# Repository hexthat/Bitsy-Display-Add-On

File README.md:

# Bitsy-Display-Add-On
OLED display for Adafruit's [ItsyBitsy](https://www.adafruit.com/?q=itsybitsy&sort=BestMatch)

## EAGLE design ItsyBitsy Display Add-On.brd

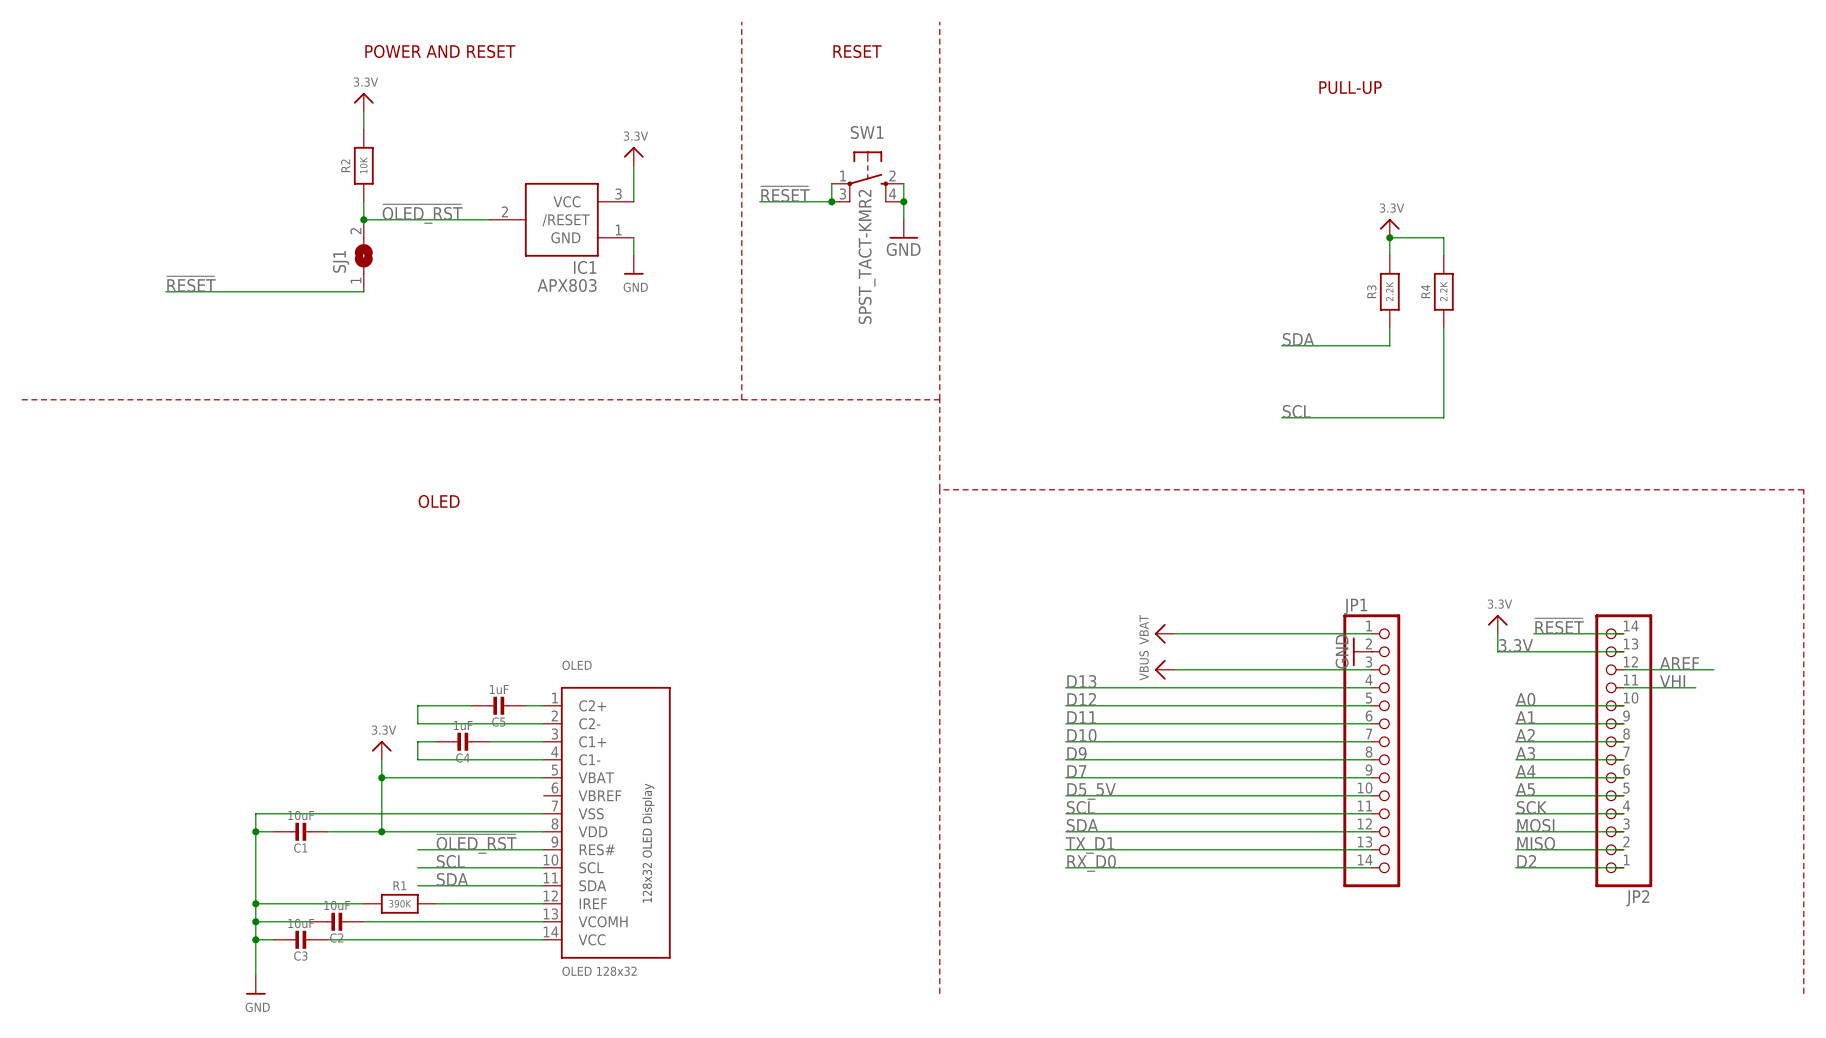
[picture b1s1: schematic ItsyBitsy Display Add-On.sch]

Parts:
C1, C2, C3: 10uF; 0805-NO
C4, C5: 1uF; 0805-NO
IC1: APX803; SOT23
JP1, JP2: HEADER-1X14; 1X14_ROUND70
OLED: OLED 128x32; UG-2832HSWEG02_WRAPUNDER
R1: 390K; 0805-NO
R2: 10K; _0805MP
R3, R4: 2.2K; 0805-NO
SJ1: SOLDERJUMPER; SOLDERJUMPER_ARROW_NOPASTE
SW1: SPST_TACT-KMR2; KMR2

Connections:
3.3V: C1.2, IC1.3 (VCC), JP2.13, OLED.5 (VBAT), OLED.8 (VDD), R2.2, R3.2, R4.2
!OLED_RST: IC1.2 (/RESET), OLED.9 (RES#), R2.1, SJ1.2
!RESET: JP2.14, SJ1.1, SW1.1, SW1.3 (P1)
A0: JP2.10
A1: JP2.9
A2: JP2.8
A3: JP2.7
A4: JP2.6
A5: JP2.5
AREF: JP2.12
C1N: C4.1, OLED.4 (C1-)
C1P: C4.2, OLED.3 (C1+)
C2N: C5.1, OLED.2 (C2-)
C2P: C5.2, OLED.1 (C2+)
D2: JP2.1
D5_5V: JP1.10
D7: JP1.9
D9: JP1.8
D10: JP1.7
D11: JP1.6
D12: JP1.5
D13: JP1.4
GND: C1.1, C2.1, C3.1, IC1.1 (GND), JP1.2, OLED.7 (VSS), R1.1, SW1.2 (S), SW1.4 (S1)
IREF: OLED.12 (IREF), R1.2
MISO: JP2.2
MOSI: JP2.3
RX_D0: JP1.14
SCK: JP2.4
SCL: JP1.11, OLED.10 (SCL), R4.1
SDA: JP1.12, OLED.11 (SDA), R3.1
TX_D1: JP1.13
VBAT: JP1.1
VBREF: OLED.6 (VBREF)
VBUS: JP1.3
VCC: C3.2, OLED.14 (VCC)
VCOMH: C2.2, OLED.13 (VCOMH)
VHI: JP2.11

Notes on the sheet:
POWER AND RESET
RESET
PULL-UP
OLED

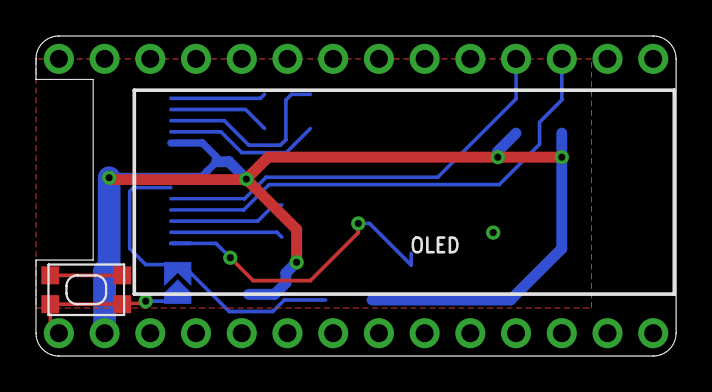
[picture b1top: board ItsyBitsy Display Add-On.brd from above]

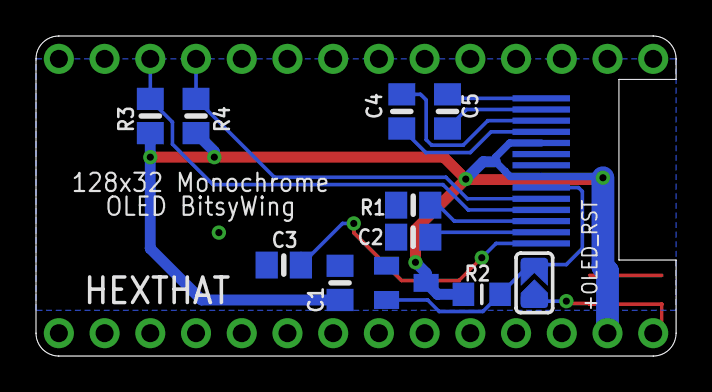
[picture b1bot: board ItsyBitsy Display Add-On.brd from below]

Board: 2 copper layers, 35.6 x 17.8 mm, 15 parts (11 on the bottom side), 13 nets.

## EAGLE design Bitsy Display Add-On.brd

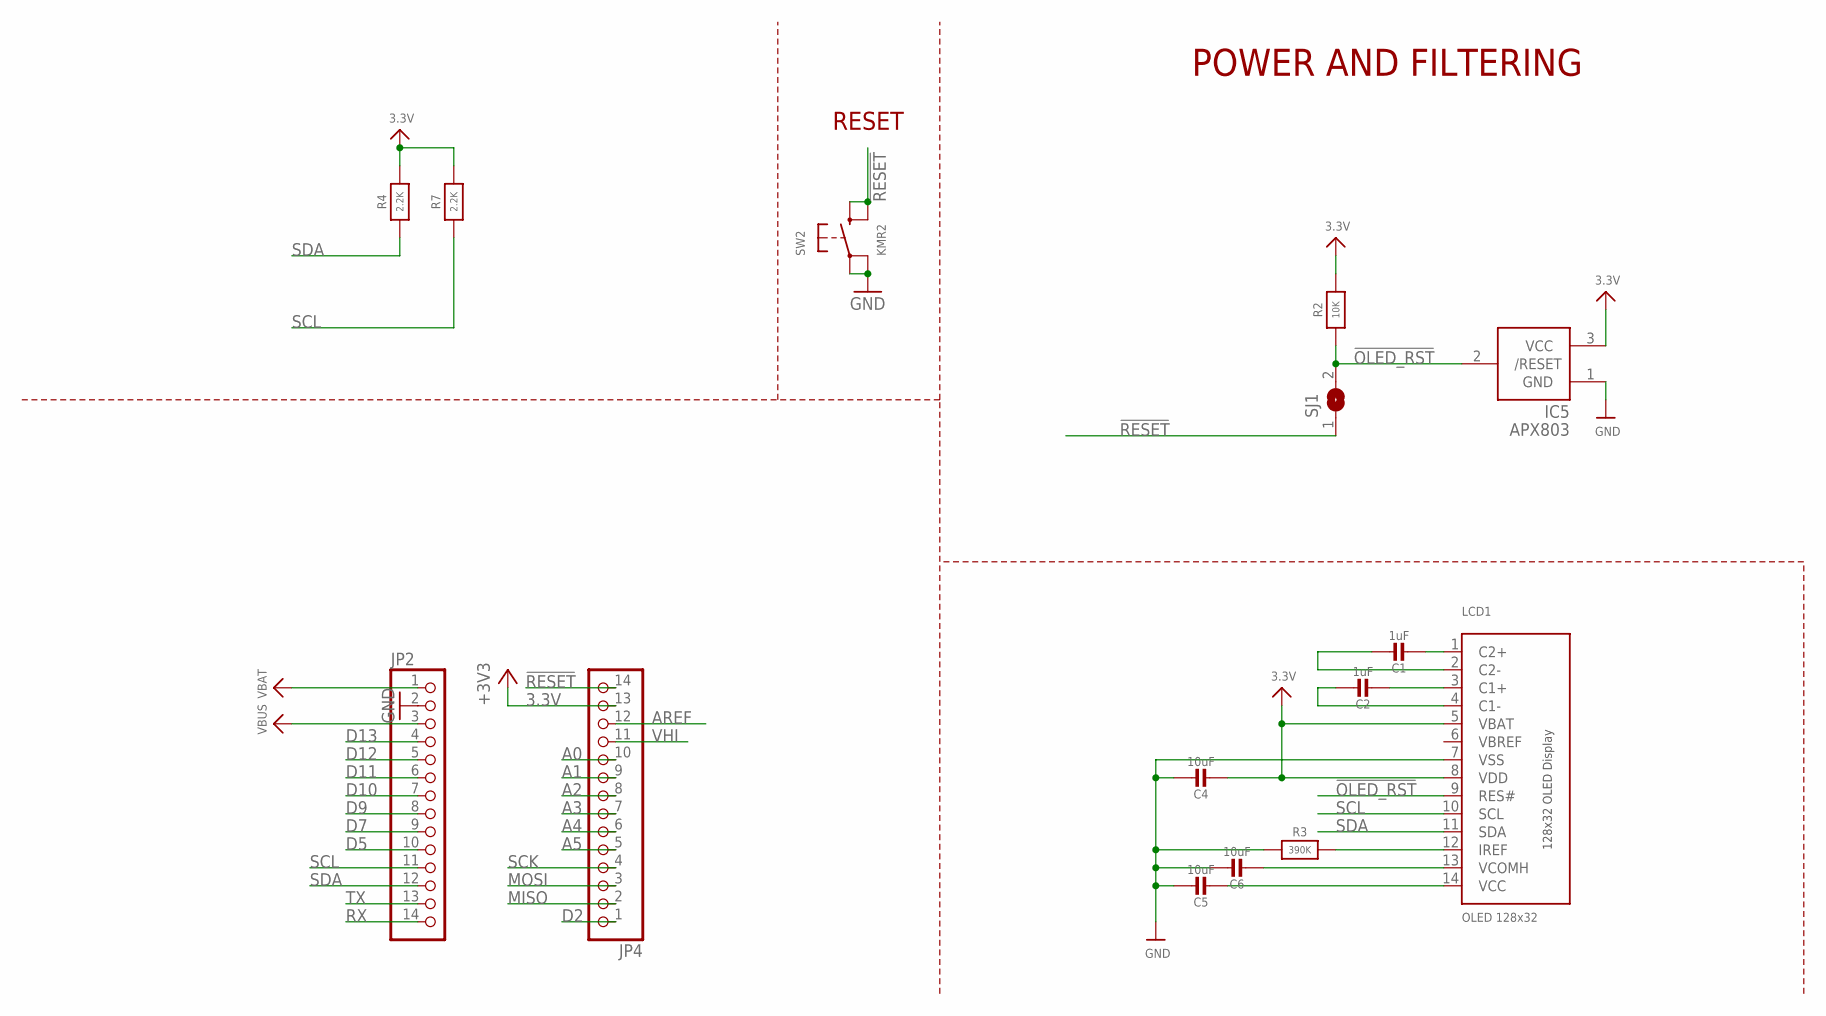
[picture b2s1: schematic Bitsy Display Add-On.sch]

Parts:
C1, C2: 1uF; 0805-NO
C4, C5, C6: 10uF; 0805-NO
IC5: APX803; SOT23
JP2, JP4: HEADER-1X14; 1X14_ROUND70
LCD1: OLED 128x32; UG-2832HSWEG02_WRAPUNDER
R2: 10K; _0805MP
R3: 390K; 0805-NO
R4, R7: 2.2K; 0805-NO
SJ1: SOLDERJUMPER; SOLDERJUMPER_ARROW_NOPASTE
SW2: KMR2; BTN_KMR2_4.6X2.8

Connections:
3.3V: C4.2, IC5.3 (VCC), JP4.13, LCD1.5 (VBAT), LCD1.8 (VDD), R2.2, R4.2, R7.2
!OLED_RST: IC5.2 (/RESET), LCD1.9 (RES#), R2.1, SJ1.2
!RESET: JP4.14, SJ1.1, SW2.B (S), SW2.B' (S1)
A0: JP4.10
A1: JP4.9
A2: JP4.8
A3: JP4.7
A4: JP4.6
A5: JP4.5
AREF: JP4.12
D2: JP4.1
D5: JP2.10
D7: JP2.9
D9: JP2.8
D10: JP2.7
D11: JP2.6
D12: JP2.5
D13: JP2.4
GND: C4.1, C5.1, C6.1, IC5.1 (GND), JP2.2, LCD1.7 (VSS), R3.1, SW2.A, SW2.A' (P1)
MISO: JP4.2
MOSI: JP4.3
unnamed: C1.2, LCD1.1 (C2+)
unnamed: C1.1, LCD1.2 (C2-)
unnamed: C2.2, LCD1.3 (C1+)
unnamed: C2.1, LCD1.4 (C1-)
unnamed: C6.2, LCD1.13 (VCOMH)
unnamed: C5.2, LCD1.14 (VCC)
unnamed: LCD1.12 (IREF), R3.2
RX: JP2.14
SCK: JP4.4
SCL: JP2.11, LCD1.10 (SCL), R7.1
SDA: JP2.12, LCD1.11 (SDA), R4.1
TX: JP2.13
VBAT: JP2.1
VBREF: LCD1.6 (VBREF)
VBUS: JP2.3
VHI: JP4.11

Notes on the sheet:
POWER AND FILTERING
RESET

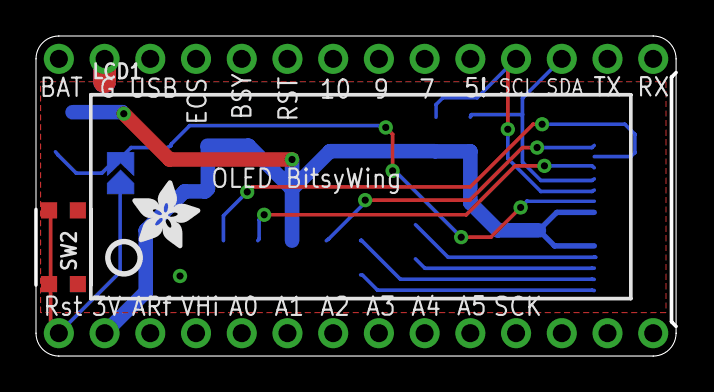
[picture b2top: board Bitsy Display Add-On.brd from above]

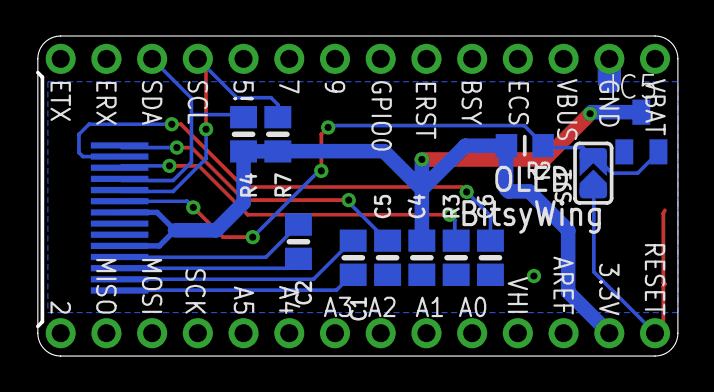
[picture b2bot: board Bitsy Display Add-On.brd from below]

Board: 2 copper layers, 35.5 x 17.6 mm, 17 parts (11 on the bottom side), 13 nets.

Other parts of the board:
U$6: PCBFEAT-REV-040
U$62: ADAFRUIT_3.5MM

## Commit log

2019-11-04 PCB
    ?
2019-11-04 PCB Redisgned
    Resistors and Capacitors on bottom of board
2019-11-05 PCB
    REV 1.0
2019-11-05 newer version
2021-11-04 Small silkscreen changes
    nothing to hardware changed
2021-11-04 images
    add images
2021-11-04 Update README.md
    add link to adafruit itsybitsy
2021-11-06 Fixed No ground to OLED, added names
2021-11-06 add info about what pad does
2021-11-06 Moved C3, flipped jumper
2021-11-06 >=16V added

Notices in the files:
parts and their libraries:
microbuilder: This work is placed in the public domain, and may be freely used for commercial and non-commercial work with the following conditions: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
